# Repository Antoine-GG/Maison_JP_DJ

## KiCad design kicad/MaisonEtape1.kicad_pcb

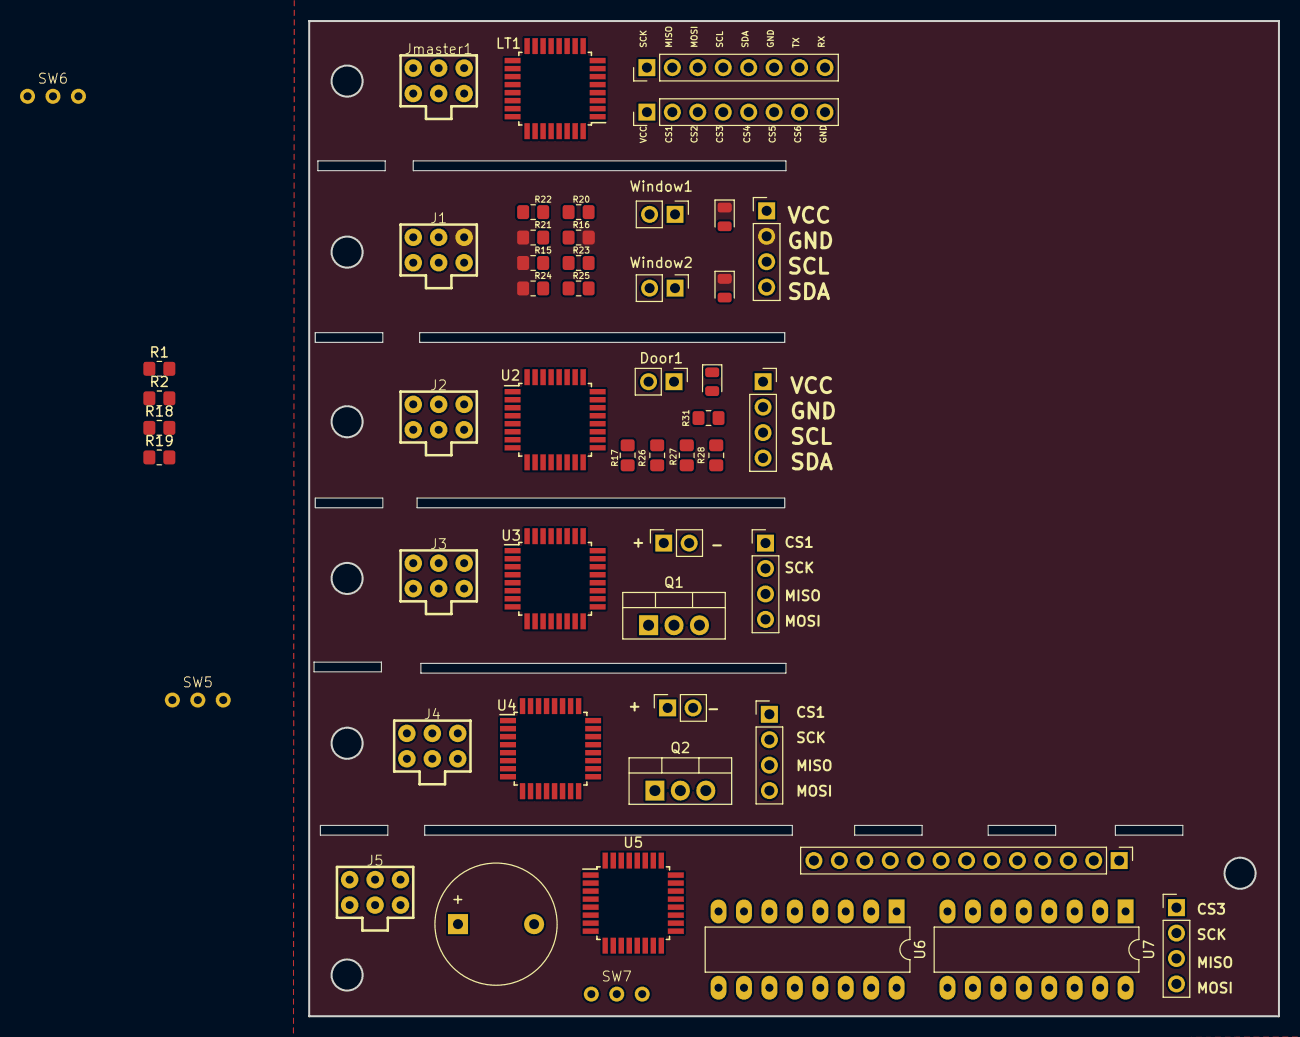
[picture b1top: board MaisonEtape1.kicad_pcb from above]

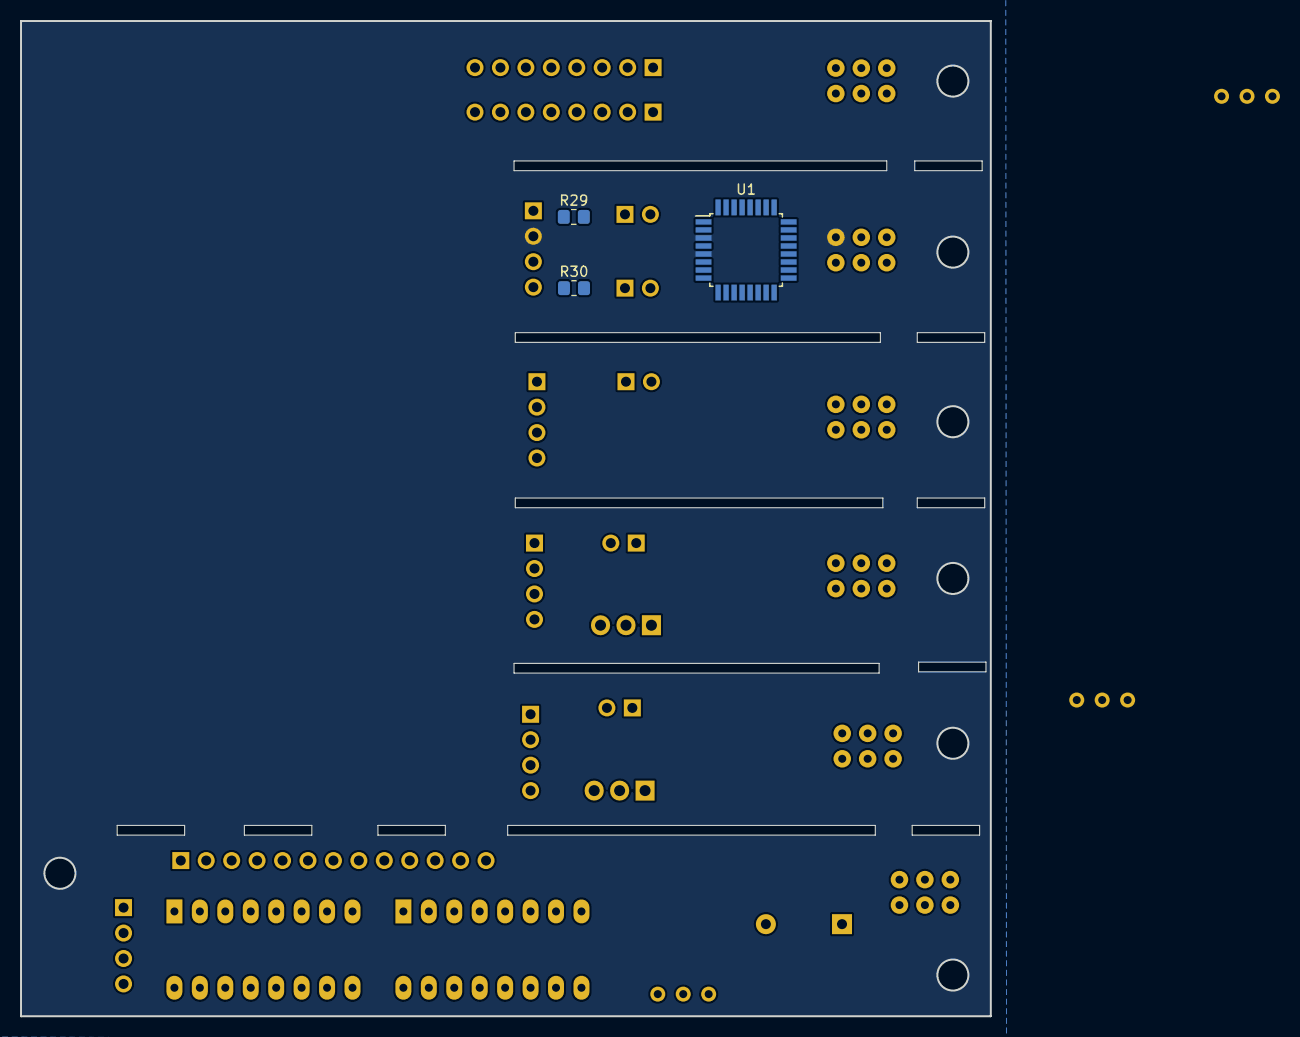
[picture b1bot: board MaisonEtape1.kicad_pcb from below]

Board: 4 copper layers, 96.8 x 99.4 mm, 55 parts (3 on the bottom side), 96 nets, no tracks yet.

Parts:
BZ1: Buzzer; Buzzer_12x9.5RM7.6
Door1: Conn_01x02_Socket; PinHeader_1x02_P2.54mm_Vertical
J1, J2, J3, J4, J5: AVR-ISP-6; SPI_prog
J10: Conn_01x13_Pin; PinHeader_1x13_P2.54mm_Vertical
J11, J12: Conn_01x02_Socket; PinSocket_1x02_P2.54mm_Vertical
J13, J14: Conn_01x08_Socket; PinHeader_1x08_P2.54mm_Vertical
J_SPI_3, J_SPI_4, J_SPI_5: SPI_SOCKET; PinHeader_1x04_P2.54mm_Vertical
J_U1: Conn_01x04_Socket; PinHeader_1x04_P2.54mm_Vertical
J_U2: Conn_01x04_Socket; PinSocket_1x04_P2.54mm_Vertical
Jmaster1: AVR-ISP-6; SPI_prog
LT1: ATmega8A-A; TQFP-32_7x7mm_P0.8mm
Q1, Q2: NMOS; TO-220-3_Vertical
R1, R19: 200R; R_0805_2012Metric_Pad1.20x1.40mm_HandSolder
R2, R18: 1K; R_0805_2012Metric_Pad1.20x1.40mm_HandSolder
R15, R16, R28: 10K; R_0805_2012Metric_Pad1.20x1.40mm_HandSolder
R17, R22, R23: 80k; R_0805_2012Metric_Pad1.20x1.40mm_HandSolder
R20, R25, R27: 220R; R_0805_2012Metric_Pad1.20x1.40mm_HandSolder
R21, R24, R26: 1.5k; R_0805_2012Metric_Pad1.20x1.40mm_HandSolder
R29, R30, R31: 220; R_0805_2012Metric_Pad1.20x1.40mm_HandSolder
SW5, SW6, SW7: SW_SPDT; BSI-10
U1, U2, U3, U4, U5: ATmega8A-A; TQFP-32_7x7mm_P0.8mm
U6, U7: 4021; DIP-16_W7.62mm_LongPads
Window1, Window2: Conn_01x02_Socket; PinHeader_1x02_P2.54mm_Vertical
Window_1, Window_2: LED; LED_0805_2012Metric
door_1: LED; LED_0805_2012Metric

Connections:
+5V: J3.2 (VCC), J4.2 (VCC), J5.2 (VCC), J10.1, Jmaster1.2 (VCC), U6.16 (Vdd), U7.16 (Vdd)
CS1: J13.2, LT1.32 (PD2)
CS2: J13.3, LT1.1 (PD3)
CS3: J13.4, LT1.2 (PD4)
CS4: J13.5, LT1.9 (PD5)
CS5: J13.6, LT1.10 (PD6)
CS6: J13.7, LT1.11 (PD7)
Clavier_clockPin: U5.24 (PC1), U6.10 (CP), U7.10 (CP)
Clavier_dataPin: U5.25 (PC2), U6.3 (Q7)
Clavier_latchPin: U5.23 (PC0), U6.9 (PL), U7.9 (PL)
GND: BZ1.2 (+), J3.6 (GND), J4.6 (GND), J5.6 (GND), Jmaster1.6 (GND), U6.8 (Vss), U6.14 (P5), U6.15 (P6), U7.8 (Vss), U7.14 (P5), U7.15 (P6)
GPIO_Lumiere: R18.1, U3.28 (PC5)
GPIO_Moteur: R2.1, U4.28 (PC5)
LT_GND: J13.8, J14.6, LT1.3 (GND), LT1.5 (GND)
LT_RESET: Jmaster1.5 (~RST), LT1.29 (PC6/~RESET)
LT_SPI_MISO: J14.2, Jmaster1.1 (MISO), LT1.16 (PB4)
LT_SPI_MOSI: J14.3, Jmaster1.4 (MOSI), LT1.15 (PB3)
LT_SPI_SCK: J14.1, Jmaster1.3 (SCK), LT1.17 (PB5)
LT_UART_RX: J14.8, LT1.30 (PD0)
LT_UART_TX: J14.7, LT1.31 (PD1)
LT_VCC: J13.1, LT1.4 (VCC), LT1.6 (VCC), LT1.18 (AVCC)
LT_i2c_SCL: J14.4, LT1.28 (PC5)
LT_i2c_SDA: J14.5, LT1.27 (PC4)
unnamed: BZ1.1 (-), U5.26 (PC3)
unnamed: Door1.1, R27.2, R28.2
unnamed: J1.1 (MISO), U1.15 (PB3)
unnamed: J1.4 (MOSI), U1.16 (PB4)
unnamed: J1.3 (SCK), U1.17 (PB5)
unnamed: J2.1 (MISO), U2.15 (PB3)
unnamed: J2.4 (MOSI), U2.16 (PB4)
unnamed: J2.3 (SCK), U2.17 (PB5)
unnamed: J11.2, Q1.1 (D)
unnamed: J12.2, Q2.1 (D)
unnamed: Q1.2 (G), R1.2, R2.2
unnamed: Q2.2 (G), R18.2, R19.2
unnamed: R17.2, R26.2, R27.1
unnamed: R20.1, R21.2, R22.2
unnamed: R23.2, R24.2, R25.1
unnamed: SW5.2 (B), U3.14 (PB2)
unnamed: SW6.2 (B), U4.14 (PB2)
unnamed: SW7.2 (B), U5.14 (PB2)
unnamed: R29.1, U1.12 (PB0)
unnamed: R30.1, U1.13 (PB1)
unnamed: R23.1, U1.10 (PD6)
unnamed: R22.1, U1.11 (PD7)
unnamed: R31.1, U2.12 (PB0)
unnamed: R17.1, U2.11 (PD7)
unnamed: U5.3 (GND), U5.5 (GND)
unnamed: U6.11 (DS), U7.3 (Q7)
unnamed: R15.1, R25.2, Window1.1
unnamed: R16.2, R20.2, Window2.1
unnamed: R29.2, Window_1.2 (A)
unnamed: R30.2, Window_2.2 (A)
unnamed: R31.2, door_1.2 (A)
QA1: J10.13, U6.7 (P0)
QA2: J10.7, U7.7 (P0)
QB1: J10.12, U6.6 (P1)
QB2: J10.6, U7.6 (P1)
QC1: J10.11, U6.5 (P2)
QC2: J10.5, U7.5 (P2)
QD1: J10.10, U6.4 (P3)
QD2: J10.4, U7.4 (P3)
QE1: J10.8, U6.13 (P4)
QE2: J10.2, U7.13 (P4)
QH1: J10.9, U6.1 (P7)
QH2: J10.3, U7.1 (P7)
U1_GND: J1.6 (GND), J_U1.2, R15.2, R16.1, R21.1, R24.1, U1.3 (GND), U1.5 (GND), Window_1.1 (K), Window_2.1 (K)
U1_RESET: J1.5 (~RST), U1.29 (PC6/~RESET)
U1_VCC: J1.2 (VCC), J_U1.1, U1.4 (VCC), U1.6 (VCC), U1.18 (AVCC), Window1.2, Window2.2
U1_i2c_SCL: J_U1.3, U1.28 (PC5)
U1_i2c_SDA: J_U1.4, U1.27 (PC4)
U2_GND: J2.6 (GND), J_U2.2, R26.1, R28.1, U2.3 (GND), U2.5 (GND), door_1.1 (K)
U2_RESET: J2.5 (~RST), U2.29 (PC6/~RESET)
U2_VCC: Door1.2, J2.2 (VCC), J_U2.1, U2.4 (VCC), U2.6 (VCC), U2.18 (AVCC)
U2_i2c_SCL: J_U2.3, U2.28 (PC5)
U2_i2c_SDA: J_U2.4, U2.27 (PC4)
U3_CS1: J_SPI_3.1, SW5.3 (C)
U3_GND: Q2.3 (S), R19.1, U3.3 (GND), U3.5 (GND)
U3_RESET: J3.5 (~RST), U3.29 (PC6/~RESET)
U3_SPI_MISO: J3.1 (MISO), J_SPI_3.3, U3.16 (PB4)
U3_SPI_MOSI: J3.4 (MOSI), J_SPI_3.4, U3.15 (PB3)
U3_SPI_SCK: J3.3 (SCK), J_SPI_3.2, U3.17 (PB5)
U3_VCC: J12.1, U3.4 (VCC), U3.6 (VCC), U3.18 (AVCC)
U4_CS2: J_SPI_4.1, SW6.3 (C)
U4_GND: Q1.3 (S), R1.1, U4.3 (GND), U4.5 (GND)
U4_RESET: J4.5 (~RST), U4.29 (PC6/~RESET)
U4_SPI_MISO: J4.1 (MISO), J_SPI_4.3, U4.16 (PB4)
U4_SPI_MOSI: J4.4 (MOSI), J_SPI_4.4, U4.15 (PB3)
U4_SPI_SCK: J4.3 (SCK), J_SPI_4.2, U4.17 (PB5)
U4_VCC: J11.1, U4.4 (VCC), U4.6 (VCC), U4.18 (AVCC)
U5_CS3: J_SPI_5.1, SW7.3 (C)
U5_RESET: J5.5 (~RST), U5.29 (PC6/~RESET)
U5_SPI_MISO: J5.1 (MISO), J_SPI_5.3, U5.16 (PB4)
U5_SPI_MOSI: J5.4 (MOSI), J_SPI_5.4, U5.15 (PB3)
U5_SPI_SCK: J5.3 (SCK), J_SPI_5.2, U5.17 (PB5)
U5_VCC: U5.4 (VCC), U5.6 (VCC), U5.18 (AVCC)

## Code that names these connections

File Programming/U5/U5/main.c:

/*
 * main.c
 *
 * Created: 9/14/2023 3:46:22 PM
 *  Author: JP Toutant, ChatGPT
 *	Prototype arduino ensuite port sur avr
 *	
 */ 


#define F_CPU 1000000UL
#include <xc.h>
#include <util/delay.h>
#include <avr/sfr_defs.h>
#include <stdlib.h>
#include <stdio.h>
#include "BuzzerSounds.h"



#define LATCH_PIN   PC0
#define CLOCK_PIN   PC1
#define DATA_PIN    PC2
#define MOSI_PIN    PB3     // MOSI: Master Out Slave In
#define MISO_PIN    PB4     // MISO: Master In Slave Out
#define SCK_PIN     PB5     // SCK: Serial Clock
#define SS_PIN      PB2     // SS: Slave Select (Chip Select)
#define DEBUG_PIN   PB0     // SS: Slave Select (Chip Select)

#define KEY_7	  0x0001
#define KEY_0002  0x0002
#define KEY_0004  0x0004
#define KEY_STAR  0x0008

#define KEY_4     0x0010
#define KEY_1     0x0020
#define KEY_0     0x0040
#define KEY_8     0x0080
#define KEY_2     0x0100
#define KEY_0200  0x0200
#define KEY_0400  0x0400
#define KEY_5     0x0800
#define KEY_SHARP 0x1000
#define KEY_9     0x2000
#define KEY_6     0x4000
#define KEY_3     0x8000

char buffer[16];

void initIOports(){
	// Initialize I/O pins
	DDRB |= (1 << PB1); // Buzzer pin as output
	DDRC |= (1 << LATCH_PIN); // Latch pin as output
	DDRC |= (1 << CLOCK_PIN); // Clock pin as output
	DDRC &= ~(1 << DATA_PIN); // Data pin as input
	//MISO as output, all others input
	DDRB |= (1 << MISO_PIN);
	//SPI inputs
	DDRB &= ~(1 << SS_PIN);
	DDRB &= ~(1 << MOSI_PIN);
	DDRB &= ~(1 << SCK_PIN);
	
	// Enable pull-up resistor for data pin
	PORTC |= (1 << DATA_PIN);
		
}
void SPI_SlaveInit(void)
{
	/* Enable SPI */
	SPCR = (1<<SPE);
}

char SPI_SlaveReceive(void)
{	
	/* Wait for reception complete */
	while(!(SPSR & (1<<SPIF)))
	;
	/* Return Data Register */
	return SPDR;
}

//initialiser UART
void initUSART(void) {
	UBRR0H = 0;              /* baud rate  */
	UBRR0L = 0x0C;           /* 9600 */
	UCSR0A |= (1 << U2X0);      /* mode asynchrone double vitesse */
	UCSR0B |= (1 << TXEN0) | (1 << RXEN0);    /* Activer emission et reception  USART */
	UCSR0C |= (1 << UCSZ01) | (1 << UCSZ00);   /* 8 data bits, 1 stop bit, valeur au reset*/
}

//transmettre un caract�re
void uartByteTransmit(uint8_t data) {
	while ( !( UCSR0A & (1<<UDRE0)) ); /* Attendre que le buffer de transmission soit vide */
	UDR0 = data;                      /* envoyer la donn�e */
}

//recevoir un caract�re
uint8_t receiveByte(void) {
	while ( !( UCSR0A & (1<<RXC0)) ); /* Attendre que le buffer de r�ception soit plein */
	return UDR0;                                /* retourner la valeur lue */
}

//envoyer une chaine de caract�res
void printString(const char myString[]) {
	uint8_t i = 0;
	while (myString[i]) {
		uartByteTransmit(myString[i]);
		i++;
	}
}

//SPI CALLS
// Function to read data from the shift registers
uint16_t readShiftRegisters() {
	uint16_t data = 0;
	
	// Latch low, fin de la dompe parallele precedente
	PORTC |= (1 << LATCH_PIN);
	_delay_us(20);
	PORTC &= ~(1 << LATCH_PIN);
	_delay_us(20);
	PORTC &= ~(1 << LATCH_PIN);
	_delay_us(20);
	// 16 clocks pour acheminer 16bits serial vers notre pin data
	for (int i = 0; i < 16; i++) {
		// Pulse the clock pin to shift in the next bit
		_delay_us(30);
		if((PINC & (1 << PC2))) data |= (1 << i);
		PORTC |= (1 << CLOCK_PIN);
		_delay_us(30);
		PORTC &= ~(1 << CLOCK_PIN);
		
		// Read the data pin and store the bit
		//data |= (PINC & (1 << DATA_PIN)) << i;
		
	}
	return data;
}

int main() {
	uint8_t feedback =0;
	initIOports();
	SPI_SlaveInit();
	initUSART();
	//sound_fail();
	//sound_input();
	//sound_success();
	while (1) {
		
		// Read data from shift registers
		uint16_t shiftRegisterData = readShiftRegisters();
		                                                                                                                                                                                                                                                                                              
		switch (shiftRegisterData)
		{
		case 0:
			SPDR = '<';
			break;
		case KEY_0:
			SPDR = '0';
			break;
		case KEY_1:
			SPDR = '1';
			break;
		case KEY_2:
			SPDR = '2';
			break;
		case KEY_3:
			SPDR = '3';
			break;
		case KEY_4:
			SPDR = '4'; 
			break;
		case KEY_5:
			SPDR = '5'; 
			break;
		case KEY_6:
			SPDR = '6';  
			break;
		case KEY_7:
			SPDR = '7';  
			break;
		case KEY_8:
			SPDR = '8'; 
			break;
		case KEY_9:
			SPDR = '9'; 
			break;
		case KEY_STAR:
			SPDR = ':';
			break;
		case KEY_SHARP:
			SPDR = ';';
			break;
		default:
			SPDR = '<';
			break;
		}
		feedback = SPI_SlaveReceive();
		switch (feedback)
		{
		case 0xF0:
			sound_input();	 
			break;
		case 0xE0:
			sound_fail();	 
			break;
		case 0xD0:
			sound_success();	 
			break;		
		default:
			break;
		}
		
		_delay_ms(1); // We need a responsive rate
	}
	return 0;
}

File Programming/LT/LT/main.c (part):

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void SPI_MasterInit(void)
{
	/* Set MOSI and SCK output SS,  */
	DDRB = (1<<PB3)|(1<<PB5)|(1<<PB2);
	// set Port C pins for 3 ss	
	DDRD = (1<<SLAVE3)|(1<<SLAVE4)|(1<<SLAVE5);
	/* Enable SPI, Master, set clock rate fck/16 */
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
//manual i2c
void initManualI2c(void){
	// Set PC4 and PC5 as output pins
	DDRC |= (1 << SDApin) | (1 << SCLpin);
	PORTC |= (1 << SDApin) | (1 << SCLpin);
	_delay_ms(1);
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			reversedByte |= (1 << (7 - i));
		}
	}
	// Output each bit of dataByte on PC4
	for (int i = 0; i < 10; i++){
		// Check the current bit and set PC4 accordingly
		if (reversedByte & (1 << i)){
			PORTC |= (1 << SDApin);  // Set PC4 high
		}
		else
		{
			PORTC &= ~(1 << SDApin); // Set PC4 low
		}

		// Create a clock pulse by toggling PC5
		PORTC |= (1 << SCLpin);
		_delay_us(10); // Adjust delay as needed for your clock frequency
		PORTC &= ~(1 << SCLpin);
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	I2C_Repeated_Start(Slave_Read_Address1);	// Repeated Start I2C communication with SLA+R
	_delay_ms(5);
	
	valFenetre=I2C_Read_Nack(); //lire la donn�e (1 seule) et envoyer sur le port D   v�rifier l'�tat de PD0
	_delay_ms(5);
	
	I2C_Stop();   // Stop I2C
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	I2C_Repeated_Start(Slave_Read_Address2);	// Repeated Start I2C communication with SLA+R
	_delay_ms(5);
	
	valPorte=I2C_Read_Nack(); //lire la donn�e (1 seule) et envoyer sur le port D   v�rifier l'�tat de PD0
	_delay_ms(5);
	I2C_Stop();   // Stop I2C
	_delay_ms(5);
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	//afficher l'�tat desporte
	//PORTE
	if ((valPorte & 0b10000000)==0b00000000) {
		PORTC |=(1<<PC0); //allumer temoin PORTE
	}
	else {
		
		PORTC &=~(1<<PC0); //eteindre Temoin Porte
	}
	_delay_ms(100);
}
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
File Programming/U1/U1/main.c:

/*
 * main.c
 *
 * Created: 9/20/2023 7:20:41 AM
 *  Author: JP Toutant
 */ 

#define F_CPU 8000000UL							/* Define CPU clock Frequency e.g. here its 8MHz */
#include <avr/io.h>								/* Include AVR std. library file */
#include <util/delay.h>							/* Include inbuilt defined Delay header file */
#include <stdio.h>								/* Include standard I/O header file */
#include <string.h>								/* Include string header file */
#include <avr/sfr_defs.h>
#include "I2C_Slave_H_File.h"					/* Include I2C slave header file */

#define Slave_Address			0x3C

int main(void)
{
	int drapeau=0;
	int8_t count = 0;
	uint8_t valeur=0b00000000;
	
	DDRB |=(1<<PB2);//temoin fenetre 2
	DDRB |=(1<<PB1);//temoin fenetre 1
	
	PORTD|=(1<<PD6);//Resistance de Rappel activé pour le Bouton Poussoir FENETRE 1
	PORTD|=(1<<PD7);//Resistance de Rappel activé pour le Bouton Poussoir FENETRE 2
	
	
	I2C_Slave_Init(Slave_Address);
	
	while (1)
	{
		//afficher les etats des fenetres sur les leds
		if (bit_is_clear(PIND,PD7))
		{
			PORTB |=(1<<PB2) ; //allumer le temoin de la fenetre 2
		} else
		{
			PORTB &=~(1<<PB2) ; //eteindre le temoin de la fenetre 2
		}
		
		if (bit_is_clear(PIND,PD6))
		{
			PORTB |=(1<<PB1) ; //allumer le temoin de la fenetre 1
		} else
		{
			PORTB &=~(1<<PB1) ; //eteindre le temoin de la fenetre 1
		}
		switch(I2C_Slave_Listen())				/* Check for any SLA+W or SLA+R */
		{
			case 0://receive
			{
				do
				{
					
					count = I2C_Slave_Receive();/* Receive data byte*/
					if(count==0x25) drapeau=1;  // vérifier si c'est 0x25 (code) alors autoriser la transmission
					PORTD=count;
					} while (count != -1);			/* Receive until STOP/REPEATED START received */
					
					break;
				}
				
				case 1://transmit
				{
					int8_t Ack_status;
					if(drapeau==1){ //si bon code envoi l'état de PD7 et PD6
						do
						{   valeur=(PIND & 0b11000000);  //valeur de PD7, et PD6
							Ack_status = I2C_Slave_Transmit(valeur);	/* Send data byte */
							
							} while (Ack_status == 0);		/* Send until Acknowledgment is received */
							
							drapeau=0;//reset pour lire une autre donnée
						}
						break;
					}
					default:
					break;
				}
			}
		}

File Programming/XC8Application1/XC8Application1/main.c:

/*
 * main.c
 *	
 *  Created: 1er Septembre 2023
 *  Author: JP Toutant et Jérémy JBDD
 */ 

/*
#include <xc.h>
#include <avr/io.h>
#define F_CPU 1000000UL
#include <util/delay.h>

unsigned int window1 = 0;
unsigned int window2 = 0;

#define SLAVE_ADDRESS_1 0x30

void i2c_init_slave(uint8_t slave_address) {
	TWAR = (slave_address << 1);	// Configurer l'adresse de l'esclave en mode lecture
	TWCR = (1 << TWEA) | (1 << TWEN);	// Activer l'interface I2C en mode esclave avec ACK
}

void i2c_start() {
	// Attendre jusqu'à ce que l'adresse soit reçue et que le bus I2C soit occupé par le maître
	while (!(TWCR & (1 << TWINT))) {
		// Peut être utilisé pour effectuer des opérations spécifiques à l'esclave si nécessaire
	}
}



void initIOports(){

	// Set PC4 and PC5 as output pin for debug 
	DDRC |= (1 << 5);
	DDRC |= (1 << 4);

	// Set PD3 and PD4 as input pins 
    DDRD &= ~(1 << 3);
    DDRD &= ~(1 << 4);

    // Enable pull-up resistors on PD3 and PD4
    //PORTD |= (1 << 3);
    //PORTD |= (1 << 4);
}

// changement de stratégie nous laissons tomber les interrupts pour simplement faire un polling
int main(void){
	initIOports();
	while(1){
		//read the state of the doors at pin 3 and 4
		window1 = PIND & (1 << 3);
		window2 = PIND & (1 << 4);
		//if the door1 is open set PC5 pin to high otherwise set it to low
		if(window1 == 0){
			PORTC |= (1 << 5);
		}else{
			PORTC &= ~(1 << 5);
		}
		if(window2 == 0){
			PORTC |= (1 << 4);
		}else{
			PORTC &= ~(1 << 4);
		}
		_delay_ms(100);
		}
	return 0;
}

*/




//////////////////////////////////////////////////////

#include <xc.h>
#include <util/twi.h>

#define F_CPU 1000000UL

#define SLAVE_ADDRESS 0x30	// définis comme Slave

//Stocker l'état des fenêtres
volatile uint8_t window1 = 0;
volatile uint8_t window2 = 0;

void i2c_init_slave(uint8_t slave_address) { //Initialise l'interface I2C en mode Slave
	TWAR = (slave_address << 1); // Configurer l'adresse de l'esclave en mode lecture
	TWCR = (1 << TWEA) | (1 << TWEN) | (1 << TWIE); // Activer l'interface I2C en mode esclave avec ACK et interruptions
}

void i2c_start() {
	// Attendre jusqu'à ce que l'adresse soit reçue et que le bus I2C soit occupé
	while (!(TWCR & (1 << TWINT))) {
		// Peut être utilisé pour effectuer des opérations spécifiques à l'esclave si nécessaire
	}
}

void i2c_stop() {
	TWCR = (1 << TWSTO) | (1 << TWINT) | (1 << TWEN);
}

void i2c_write(uint8_t data) {		//Permet d'écrire des données dans le registre de données I2C (TWDR)
	TWDR = data;
	TWCR = (1 << TWEN) | (1 << TWINT);
}

void i2c_ack() {		//Envoie un acknowledge pour dire : Slave prêt a recevoir données 
	TWCR |= (1 << TWEA) | (1 << TWINT);
}

void i2c_nack() {		//Attend que les données soient disponibles, puis les lit et les renvoie
	TWCR = (1 << TWINT) | (1 << TWEN);
}

void initIOports(){

	// Set PC4 and PC5 as output pin for debug
	DDRC |= (1 << 5);
	DDRC |= (1 << 4);

	// Set PD3 and PD4 as input pins
	DDRD &= ~(1 << 3);
	DDRD &= ~(1 << 4);

	// Enable pull-up resistors on PD3 and PD4
	//PORTD |= (1 << 3);
	//PORTD |= (1 << 4);
}

uint8_t i2c_read() {
	TWCR = (1 << TWEN) | (1 << TWINT) | (1 << TWEA);
	while (!(TWCR & (1 << TWINT))) {
		// Peut être utilisé pour effectuer des opérations spécifiques à l'esclave si nécessaire
	}
	return TWDR;		//donnée que l'esclave a reçue du maître
}


ISR(TWI_vect) {		//réception de données et les stocke dans les variables window1 et window2
	uint8_t status = TWSR & 0xF8;

	switch (status) {
		case TW_SR_SLA_ACK: // Adresse Maitre reçue
			i2c_ack();
			break;

		case TW_SR_DATA_ACK: // Données reçues
			uint8_t receivedData = TWDR;
		
			// stocker les données reçues
			window1 = receivedData & (1 << 0);
			window2 = receivedData & (1 << 1);

			i2c_ack(); // Envoyer un ACK pour indiquer que nous sommes prêts à recevoir plus de données
			break;

		default:
			i2c_nack(); // Envoyer un NACK en cas d'erreur ou de condition non gérée
			break;
	}
}


int main(void) {
	i2c_init_slave(SLAVE_ADDRESS);
	initIOports();
	
	sei(); // Activer les interruptions globales
	
	while (1) {
		// La communication I2C est gérée par les interruptions
		
		//read the state of the doors at pin 3 and 4
		window1 = PIND & (1 << 3);
		window2 = PIND & (1 << 4);
		//if the door1 is open set PC5 pin to high otherwise set it to low
		if(window1 == 0){
			PORTC |= (1 << 5);
			}else{
			PORTC &= ~(1 << 5);
		}
		if(window2 == 0){
			PORTC |= (1 << 4);
			}else{
			PORTC &= ~(1 << 4);
		}
		_delay_ms(100);
	}
	
	return 0;
}

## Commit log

2023-08-31 Commit 1
2023-08-31 jps commit
2023-08-31 commit de jp
2023-08-31 Commit2_test
2023-08-31 commise
2023-08-31 Test chez moi
2023-08-31 Test_maison
2023-09-01 Modif_TEST_DJ
2023-09-01 kicad files
    kicad files
2023-09-01 new try
2023-09-01 OK c cool
2023-09-01 kicad to Jeremy
2023-09-01 Kicad add calvier / moteur
2023-09-01 Premier upload de code
    test pour les fenetre marche pas bien
2023-09-07 Door2 dans Main Loop
2023-09-07 Door2 Main Loop
2023-09-07 Photon
2023-09-07 New code for polling and it works
2023-09-08 Connecteur AVR + Branchement MOSI/MISO/SCK + CS
2023-09-08 Initial_code_LT
2023-09-11 work on U1
2023-09-11 deleet
2023-09-11 branchement du clavier
2023-09-13 changed CD4021 to 74HC299
2023-09-14 Programme Master à voir/tester
2023-09-14 Code LT (Build OK) + Code Slave1 + I2C
2023-09-15 Rename/cleanup
2023-09-15 debug U1
2023-09-15 clavier re-update with 4021
2023-09-15 U5 initial
2023-09-15 updates U1 LT
2023-09-15 update LT
2023-09-15 LT_update
2023-09-17 update sur tout le schema
2023-09-17 Initial code UART1(Master) + UART2(Slave)
2023-09-20 u2 initial
2023-09-21 more I2c experiments
2023-09-21 librairie i2c de Idir
2023-09-21 idi i2c library et autres
2023-09-21 LT A FAIT ALLUMER U1 HOLYSHIT
2023-09-21 ESP32 initial commit
2023-09-21 ESP32 initial
2023-09-21 update ESP32
2023-09-23 updates clavier
2023-09-24 U5 done waiting for progress on SPI
2023-09-25 ceci est un commit
2023-09-25 i2c fonctionne
2023-09-27 SPI/ I2C impletements into LT
2023-09-29 cleanup folders
2023-09-29 uart tester for the ESP32
2023-09-29 Travail sur ESP32
2023-09-29 we have good SPI running. thats nuts
2023-10-04 updates U1 pour les mauvais etats
2023-10-05 tentative reparation i2c
2023-10-05 tentative de corriger i2c
2023-10-06 10-06
2023-10-06 2 characters not working from U5, fixing
2023-10-06 update U5
2023-10-13 13-10
2023-10-19 dele esp32
2023-10-19 i2cCode
2023-10-20 update kicad
2023-10-20 updateU1U2
2023-10-20 kicadery
2023-10-20 uupdate LT
2023-10-20 idiri2c
2023-10-20 update friday pcb
2023-10-26 kicad update, finalizing
2023-10-26 ESP32 backup
2023-10-26 Delete kicad/MaisonEtape1-backups directory
    deleet backup folders
2023-10-26 change()
2023-10-26 update code Jp
2023-10-26 merge
2023-10-26 kicad
2023-10-26 kicadchange
2023-10-26 update U6
2023-10-26 cute monkeys desu
2023-11-03 switch to SPIs
2023-11-03 update SPI
2023-11-03 friday
2023-11-09 production files
